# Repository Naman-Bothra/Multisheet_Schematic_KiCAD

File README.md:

# Multisheet_Schematic_KiCAD
my first Multi sheet schematic in KiCAD
 Custom Arduino Uno Shield with L7805 Voltage Regulation & Status Indications

A professional, multi-sheet hierarchical hardware project designed in **KiCad E.D.A. 10.0.3**. This project implements an Arduino Uno-compatible expansion board featuring robust linear voltage regulation (`12V` down to `5V`), dedicated local power networks, and software-controlled LED diagnostic indicators.

---

## 🗺️ Project Architecture & Hierarchical Structure

The design follows a clean, modular multi-sheet schematic layout to maximize maintainability, isolate sub-circuits, and conform to industrial engineering standards.

```
Root (page 1)
 ├── J1 (12V Power Input Header)
 ├── J2 (5V Power Output Header)
 ├── Power (page 2)
 │    ├── Regulator (page 4): L7805 Linear Regulator Circuit
 │    └── Indications (page 5): Power & Diagnostic LED Array
 └── MCU (page 3): Arduino Uno R3 Footprint Interface
```

### 📄 Sheet Breakdown
1. **Root (Sheet 1):** Serves as the top-level block design interconnecting external input/output headers (`J1` for `12VIn` and `J2` for `5Vlocal`) with sub-sheets.
2. **Power (Sheet 2):** Intermediate bus routing layout connecting voltage processing directly with current-limiting diagnostic blocks.
3. **MCU Interface (Sheet 3):** Bridges the system connections to the **Arduino UNO R3** footprint. Features a clean, completely mapped pin configuration utilizing hierarchical labels.
4. **Regulator (Sheet 4):** Houses the **L7805 Linear Regulator (`U1`)**, input filtering capacitor (`C1`), and output smoothing capacitor (`C2`) alongside power-rail flags (`PWR_FLAG`).
5. **Indications (Sheet 5):** Features current-limiting resistors (`R1`, `R2`) driving two system LEDs (`D1` for constant `5V` power confirmation, `D2` for micro-controlled `MCULed` system heartbeat).

---

## ⚙️ Hardware Specifications & Net Mapping

### 🧩 Component Bill of Materials (BOM) Summary
| Designator | Component Name | Package / Footprint | Functional Description |
| :--- | :--- | :--- | :--- |
| **U1** | L7805 | TO-220 | +5V Linear Voltage Regulator |
| **A1** | Arduino_UNO_R3 | Standard Arduino Uno R3 Shield | Primary Processing Unit Interface |
| **C1** | Capacitor (C) | Surface-Mount / Through-Hole | Input Decoupling & Stability Ripple Filter |
| **C2** | Capacitor (C) | Surface-Mount / Through-Hole | Output High-Frequency Noise Filter |
| **R1, R2** | Resistor (R) | SMD/SMT | Current Limiting for Status Indicator LEDs |
| **D1** | LED | Standard Indicator | Constant Power Indicator (`5Vind`) |
| **D2** | LED | Standard Indicator | Microcontroller Status Indicator Pin `A0` (`MCULed`) |
| **J1, J2** | Conn_01x02_Pin | 1x02 2.54mm Pin Header | External Power & Signal Interconnect Junctions |

### ⚡ Critical Net Rail Configurations
* **`12Vin`**: High-voltage input channel feeding directly into Pin 1 (`IN`) of the L7805 regulator.
* **`5Vop` / `5Vlocal`**: Regulated quiet +5V output rail generated by Pin 3 (`OUT`) of the L7805, providing system power.
* **`5Vind`**: Dedicated status power bus running directly through current-limiting resistor `R1` to confirm active voltage regulation.
* **`MCULed`**: Targeted control net bound to Pin 9 (`A0`) of the Arduino Uno, enabling custom software-defined blink behaviors on LED `D2`.
* **`GND`**: Unbroken global ground distribution network shared across all functional blocks via specialized copper planes.

---

## 🎨 PCB Layout & Manufacturing Details

The physical board layout incorporates industrial design rules configured for 2-layer fabrication layout efficiency.

* **Layer Stackup:** 2-Layer Board (`F.Cu` Front Copper, `B.Cu` Bottom Copper).
* **Ground Strategy:** Dual-sided solid Ground planes (`GND`) configured on both the top and bottom layers to drastically reduce EM noise loop areas, maximize heat dissipation for the TO-220 package, and streamline trace routing.
* **Thermal Relief Design:** Set up with custom thermal relief connections (`0.5mm` gap clearances / `0.25mm` minimum width) on all ground-plane-connected pads to prevent cold-solder structural failures during assembly.
* **Trace Optimization:** Power routing features widened high-current traces to minimize impedance drops from the `12V` input to the regulation circuit.

---

## 🚀 Key Implementation & KiCad Settings Verified
* **ERC Clean Workflow:** Fully resolved initial reference designator conflicts (`#PWR?` duplicates) via programmatic schema annotations.
* **No-Net Island Prevention:** Cleanly avoided floating copper traps by mapping both copper zones to the global `GND` net layer, stabilizing high-frequency characteristics.
* **No-Connect Cleanliness:** All unused digital and analog pins on the `A1` microcontroller header explicitly utilize individual `No-Connect` cross-markers (`X`) to ensure predictable system behaviors.

---

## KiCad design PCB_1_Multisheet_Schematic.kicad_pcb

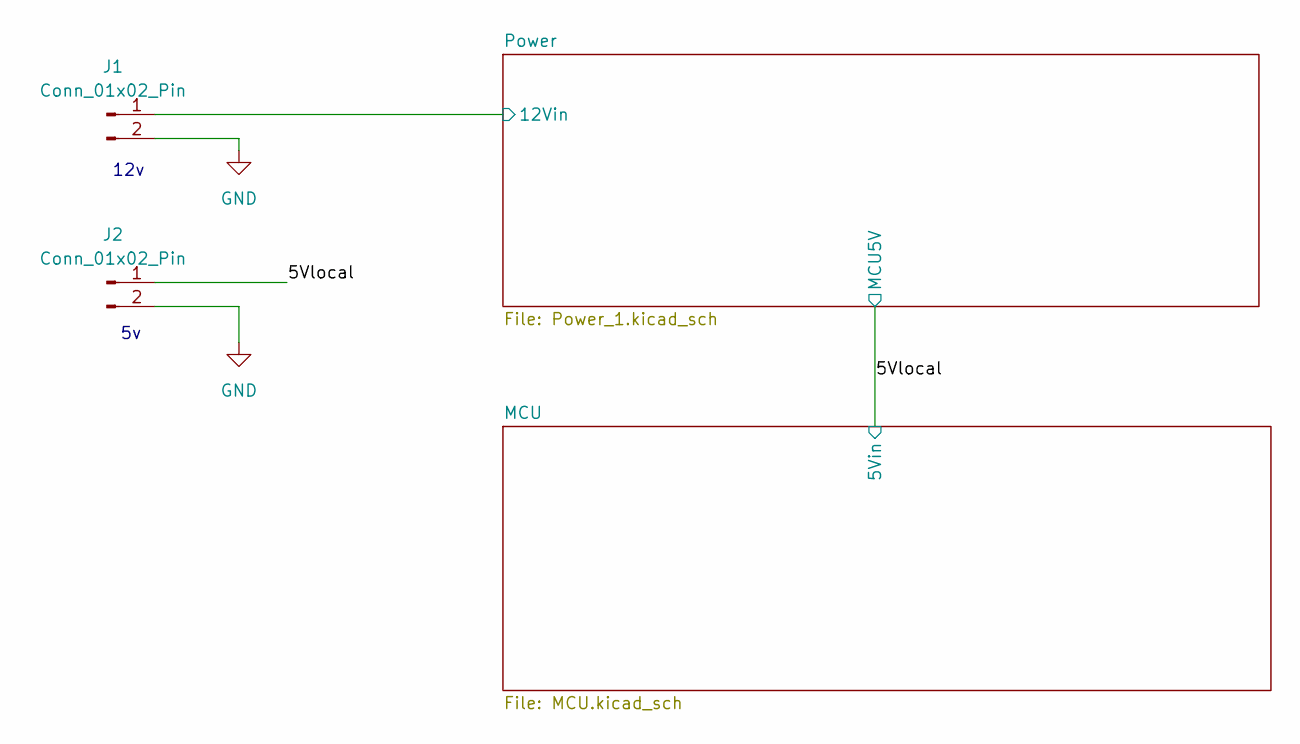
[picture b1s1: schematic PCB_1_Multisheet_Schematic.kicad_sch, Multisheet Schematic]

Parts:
J1, J2: Conn_01x02_Pin; PinHeader_1x02_P2.54mm_Horizontal

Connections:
/5Vlocal: J2.1; also elsewhere on the board
/Power/12Vin: J1.1; also elsewhere on the board
GND: J1.2, J2.2; also elsewhere on the board

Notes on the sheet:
12v

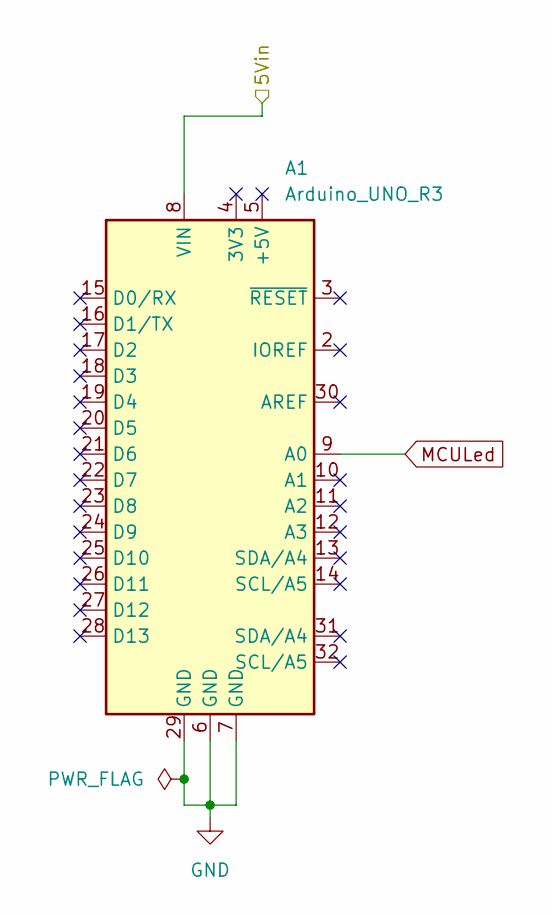
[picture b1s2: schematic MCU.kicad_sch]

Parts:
A1: Arduino_UNO_R3

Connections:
/5Vlocal: A1.8 (VIN); also elsewhere on the board
GND: A1.6 (GND), A1.7 (GND), A1.29 (GND); also elsewhere on the board
MCULed: A1.9 (A0); also elsewhere on the board

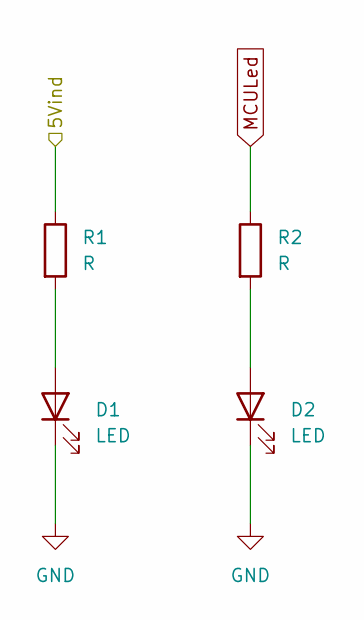
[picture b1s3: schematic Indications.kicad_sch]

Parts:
D1, D2: LED; LED_0805_2012Metric
R1, R2: R; R_1206_3216Metric

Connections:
/5Vlocal: R1.1; also elsewhere on the board
GND: D1.1 (K), D2.1 (K); also elsewhere on the board
MCULed: R2.1; also elsewhere on the board
unnamed: D1.2 (A), R1.2
unnamed: D2.2 (A), R2.2

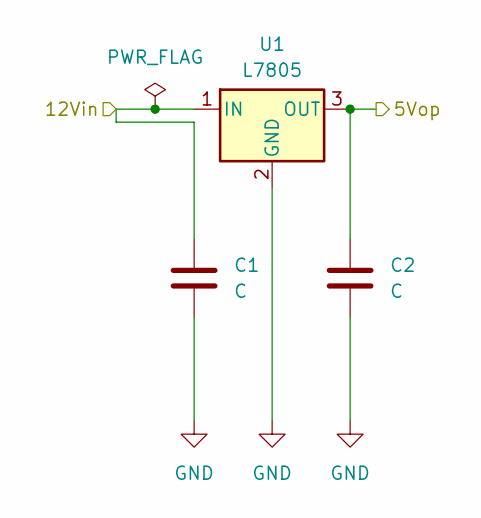
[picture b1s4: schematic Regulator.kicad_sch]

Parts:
C1, C2: C; C_1210_3225Metric
U1: L7805; TO-220-3_Vertical

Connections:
/5Vlocal: C2.1, U1.3 (OUT); also elsewhere on the board
/Power/12Vin: C1.1, U1.1 (IN); also elsewhere on the board
GND: C1.2, C2.2, U1.2 (GND); also elsewhere on the board

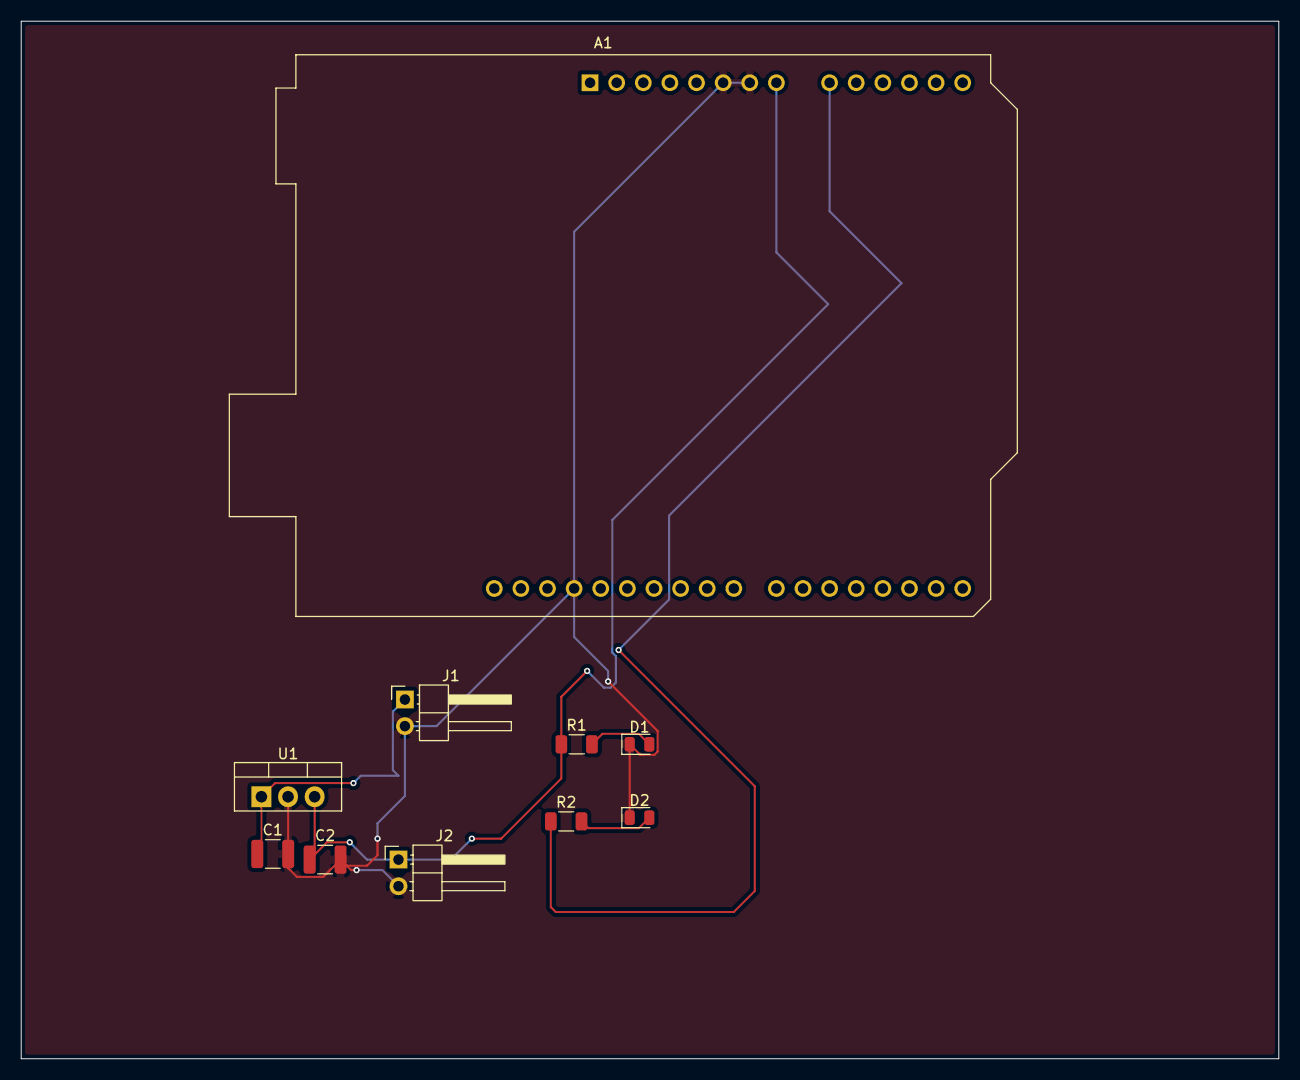
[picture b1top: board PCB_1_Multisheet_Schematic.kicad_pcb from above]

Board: 2 copper layers, 120.0 x 99.0 mm, 10 parts (0 on the bottom side), 6 nets.

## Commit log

2026-06-25 Multisheet_Schematic.md
